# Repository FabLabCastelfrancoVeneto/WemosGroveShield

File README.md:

# WemosGroveShield

Shield per Wemos D1 mini per collegare fino a 6 dispositivi Grove. || Simple shield to connect up to 6 Grove device to a Wemos D1 mini.

## Più informazioni || More info

Questo shield è predisposto per:
- collegamento di 6 connettori (preferibilmente a 90° [1] per permettere sovrapposizione di ulteriori shield)
- collegamento tramite connettori a vite di fonte esterna di tensione superiore a 5v, regolata da breakout board con MP1584EN [2]

Vengono pubblicati i piedini: A0, D1 (combinato con D2 per eventuale utilizzo della porta come I2C), D3, D5, D6, D7.
In questo modo vengono anche lasciati liberi i pin usati da shield ufficiali (es: il D4 usato dallo shield DHT22, o il D8 usato da relay shield, etc).
Abbiamo realizzato i primi prototipi con la nostra cirqoid (una cnc per pcb) e qualche test, abbiamo fatto fare un batch di pcb!

||

This shield allow you to connect:
- up to 6 connectors (better if the 90 degrees ones [1], so you can still use more shields on top of this)
- a voltage higher than 5v using a screw terminal, connected to a MP1584EN step-down module [2]

Used pins: A0, D1 (together with D2 on the same connector, so you can use it for I2C), D3, D4, D6, D7.
We have done the first prototypes with our Cirqoid (a cnc for pcb)and after a few test, we ordered a pcb batch!

[1] https://www.seeedstudio.com/Grove---Universal-4-pin-connector-90%C2%B0%2810-PCs%29-p-790.html  
[2] https://www.amazon.it/Regolabile-Buck-Converter-Step-Pezzi/dp/B01MQGMOKI/ref=sr_1_4?rps=1&ie=UTF8&qid=1531129949&sr=8-4&keywords=MP1584EN  

## Authors
* **Mirco Piccin** -  [pictux](https://github.com/pictux)

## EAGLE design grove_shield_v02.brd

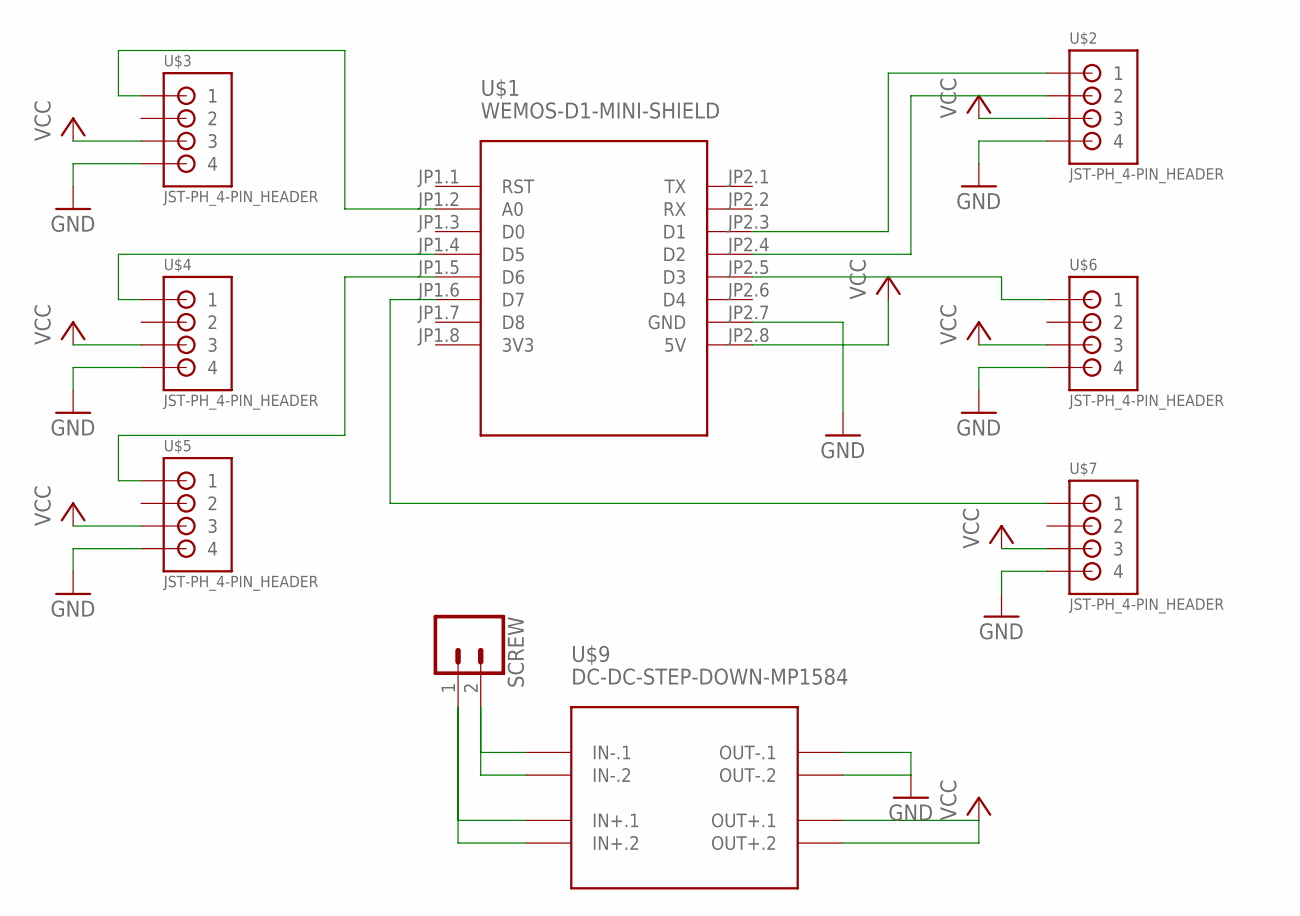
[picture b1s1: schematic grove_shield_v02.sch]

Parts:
SCREW: CONN_025MM; SCREWTERMINAL-5MM-2
U$1: WEMOS-D1-MINI-SHIELD
U$2, U$3, U$4, U$5, U$6, U$7: JST-PH_4-PIN_HEADER; JST_B4B-PH_HEADER
U$9: DC-DC-STEP-DOWN-MP1584

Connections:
3V3: U$1.JP1.8 (3V3)
GND: U$1.JP2.7 (GND), U$2.P4 (4), U$3.P4 (4), U$4.P4 (4), U$5.P4 (4), U$6.P4 (4), U$7.P4 (4), U$9.OUT-.1, U$9.OUT-.2
unnamed: SCREW.2, U$9.IN-.1, U$9.IN-.2
unnamed: U$1.JP2.5 (D3), U$6.P1 (1)
unnamed: U$1.JP2.3 (D1), U$2.P1 (1)
unnamed: U$1.JP2.4 (D2), U$2.P2 (2)
unnamed: U$1.JP1.6 (D7), U$7.P1 (1)
unnamed: U$1.JP1.2 (A0), U$3.P1 (1)
unnamed: U$1.JP1.4 (D5), U$4.P1 (1)
unnamed: U$1.JP1.5 (D6), U$5.P1 (1)
unnamed: SCREW.1, U$9.IN+.1, U$9.IN+.2
VCC: U$1.JP2.8 (5V), U$2.P3 (3), U$3.P3 (3), U$4.P3 (3), U$5.P3 (3), U$6.P3 (3), U$7.P3 (3), U$9.OUT+.1, U$9.OUT+.2

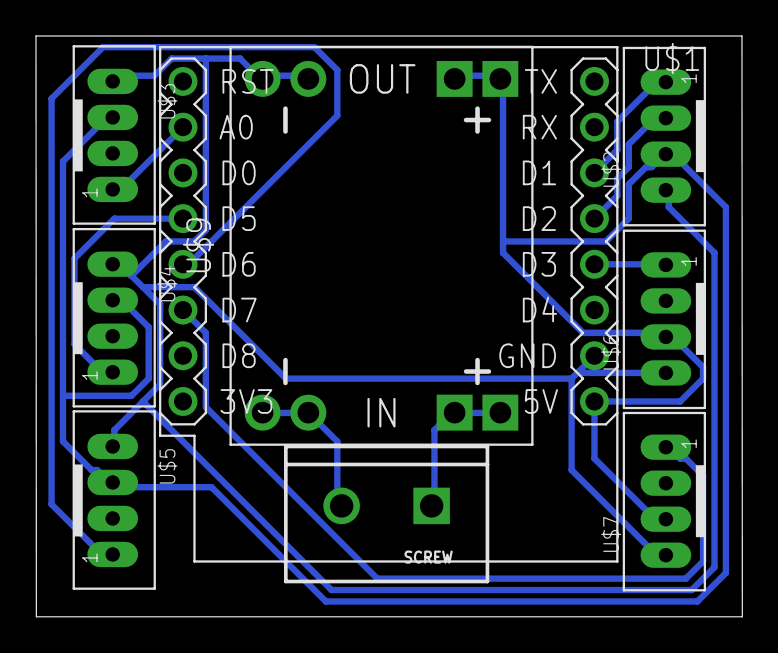
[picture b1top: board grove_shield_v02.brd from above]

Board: 2 copper layers, 39.2 x 32.3 mm, 9 parts (0 on the bottom side), 11 nets.

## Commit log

2018-08-01 eagle files commit
2018-08-01 Update README.md
    Inserita una foto della prima versioen dello shield
2018-08-01 Update README.md
    Aggiunto autore
2020-01-26 Added pcb pic

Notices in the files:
parts and their libraries:
SparkFun-Connectors: Licensing: Creative Commons ShareAlike 4.0 International - https://creativecommons.org/licenses/by-sa/4.0
diy-modules: Released under the Creative Commons Attribution 4.0 International License: http://creativecommons.org/licenses/by/4.0
